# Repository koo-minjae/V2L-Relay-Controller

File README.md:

# V2L-Relay-Controller
STM32-based relay controller with manual and automatic control modes

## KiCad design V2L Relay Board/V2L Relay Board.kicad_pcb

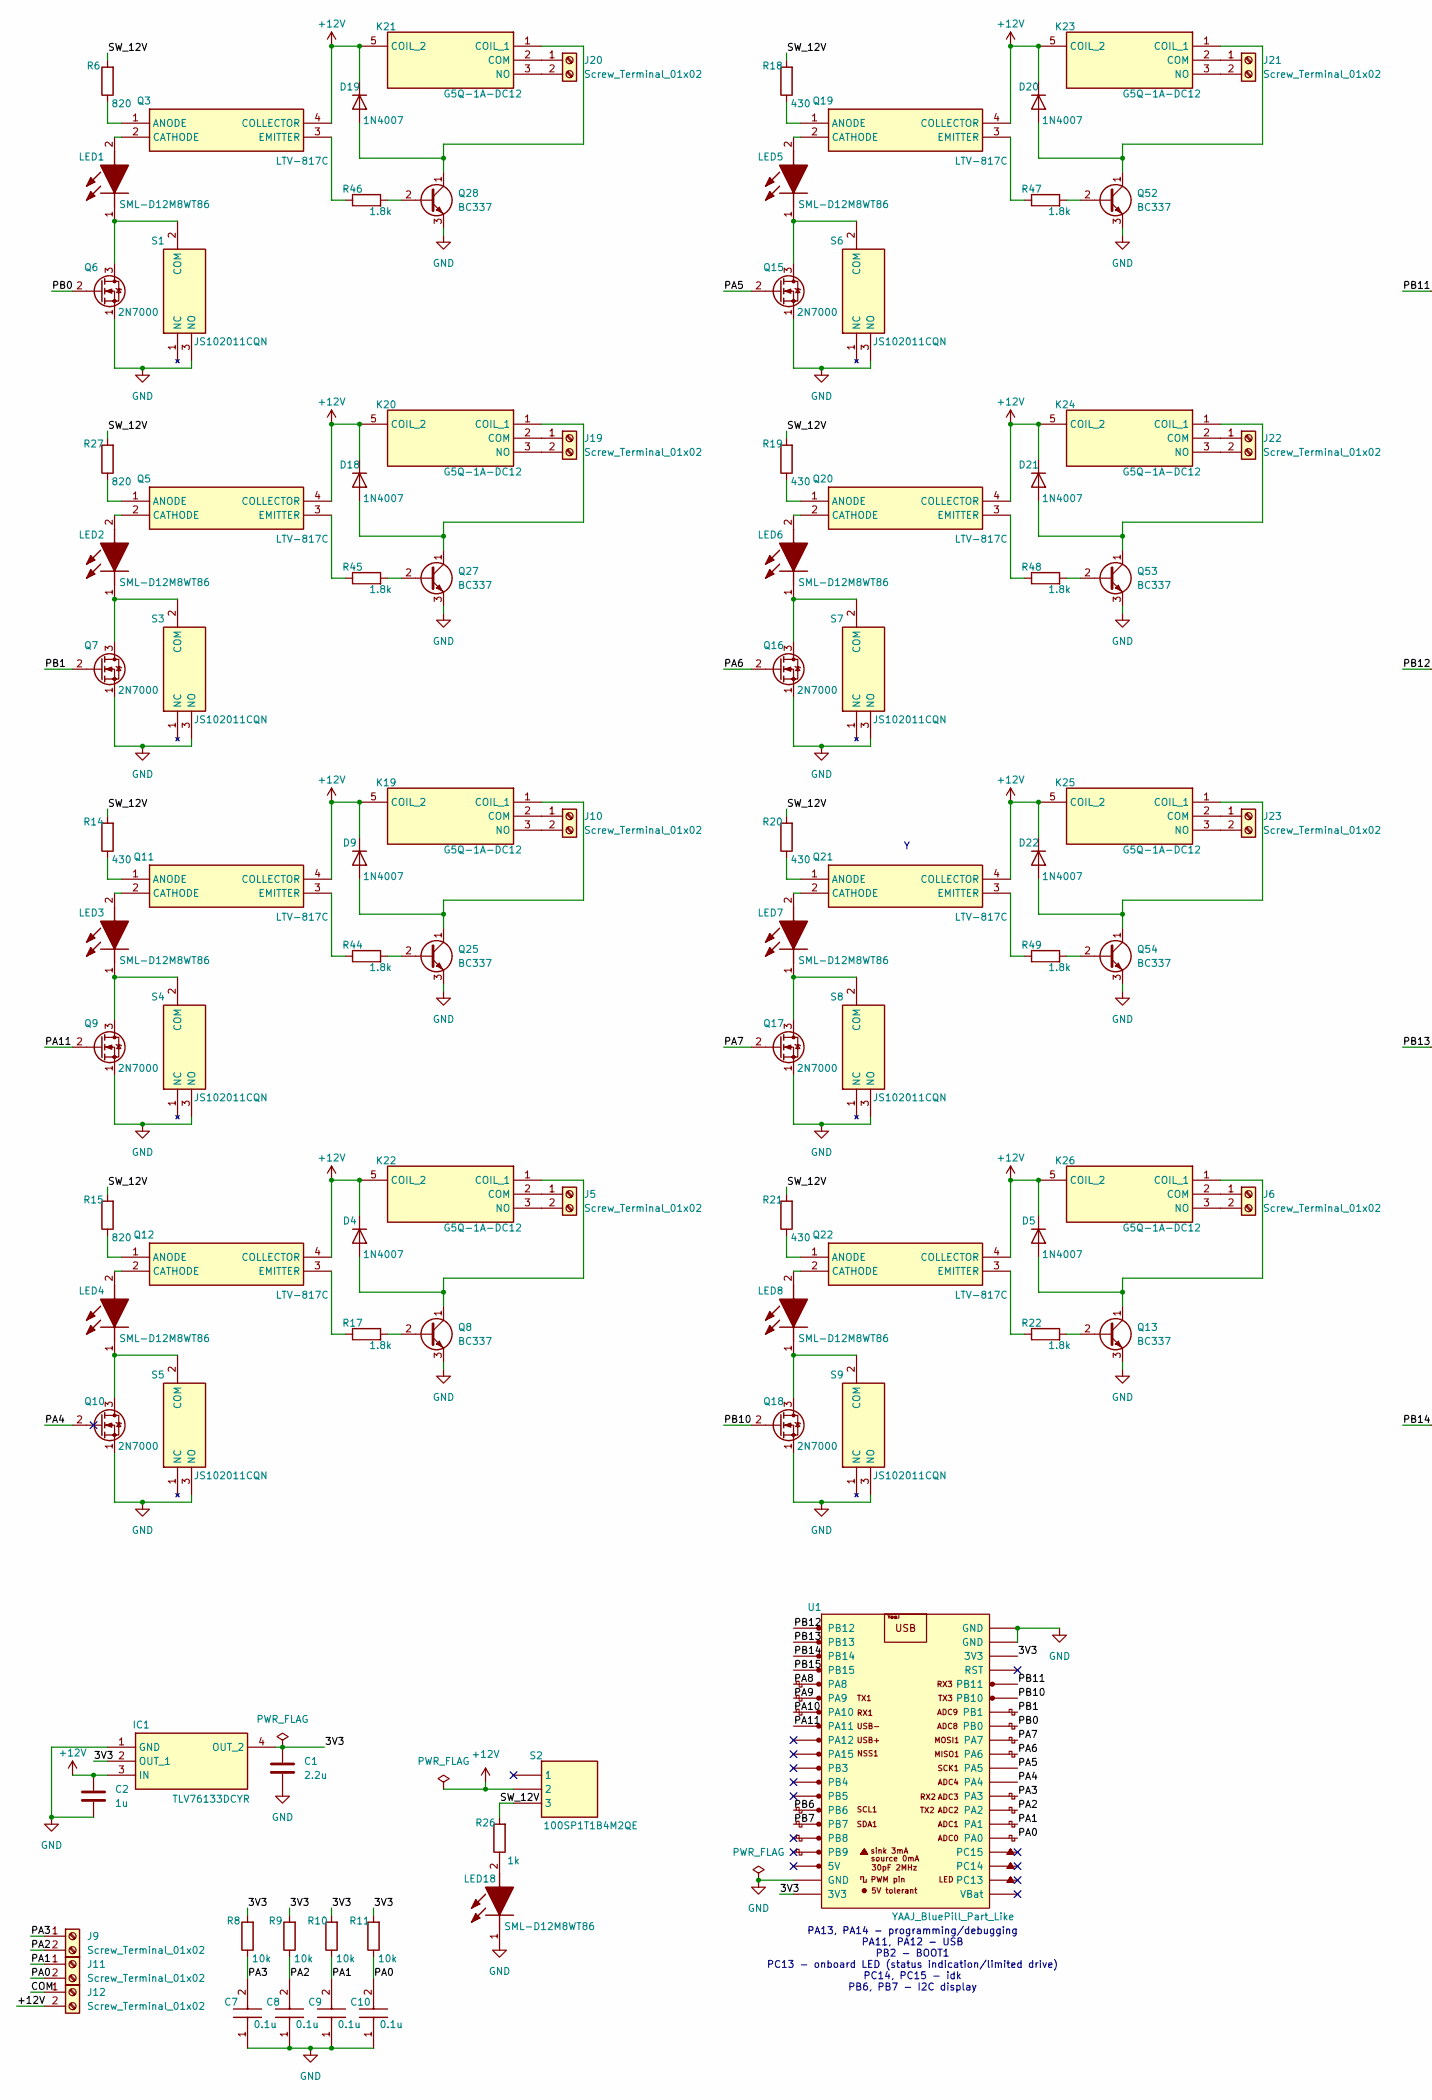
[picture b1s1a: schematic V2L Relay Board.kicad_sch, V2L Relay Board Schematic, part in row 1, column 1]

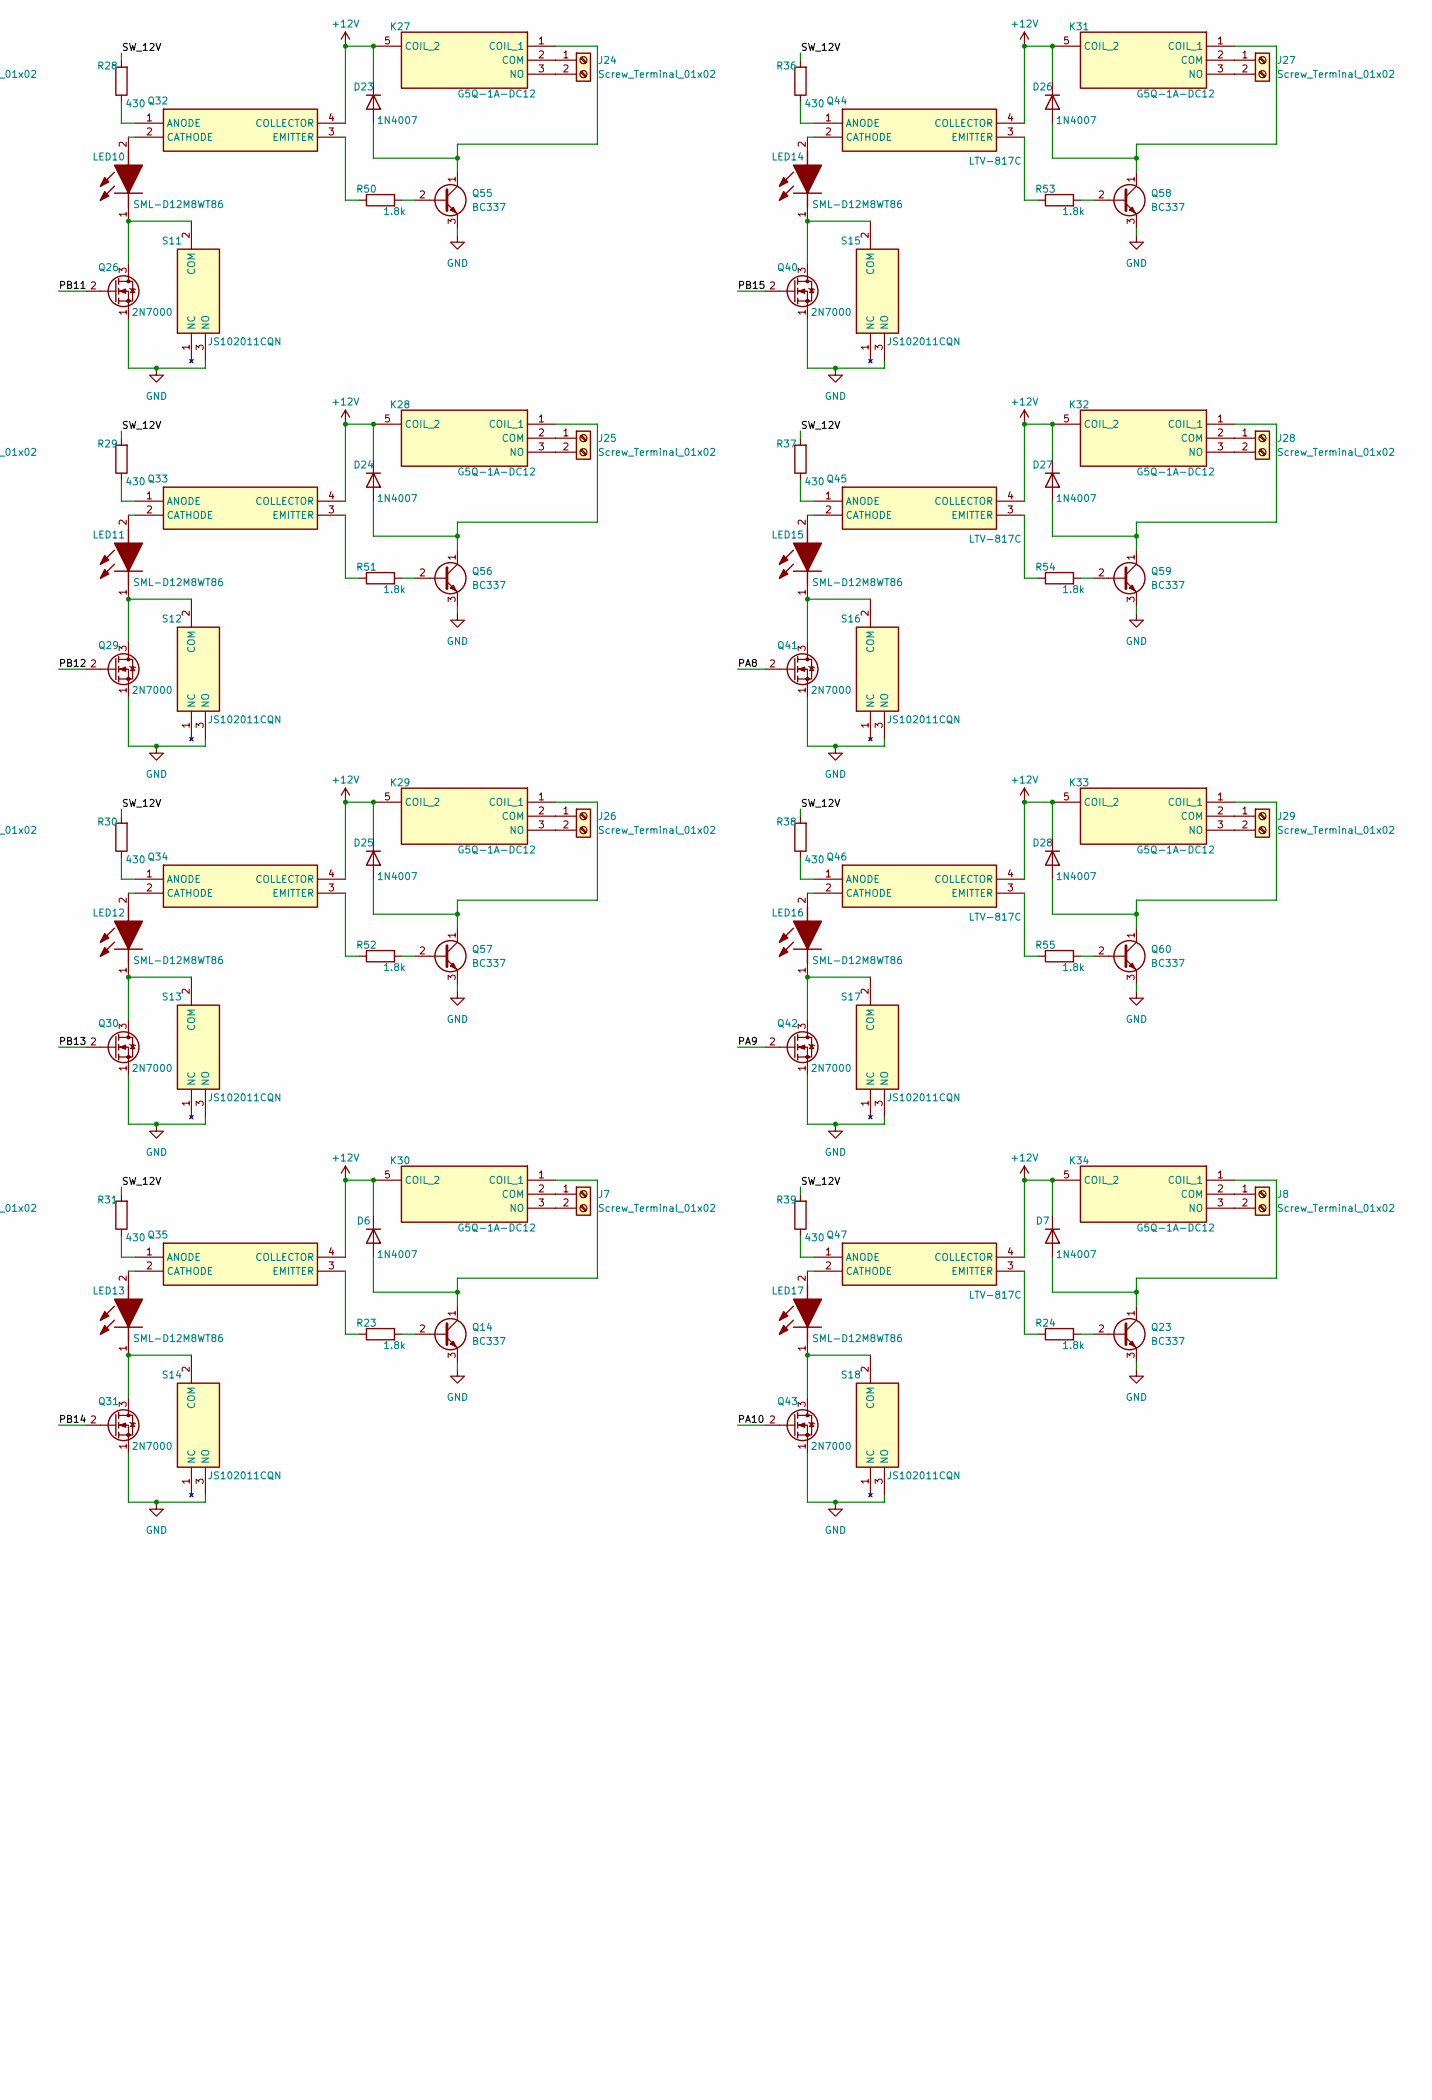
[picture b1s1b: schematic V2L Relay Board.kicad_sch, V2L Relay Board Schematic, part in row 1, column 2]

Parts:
C1: 2.2u; ZRB15x
C2: 1u; CAPC0603X35N
C7, C8, C9, C10: 0.1u; CAPC1005X60N; Manufacturer_Part_Number CL05B104KBD6PJC
D4, D5, D6, D7, D9, D18, D19, D20, D21, D22, D23, D24, D25, D26, D27, D28: 1N4007; D_DO-41_SOD81_P10.16mm_Horizontal
IC1: TLV76133DCYR; SOT230P700X180-4N; Mouser Part Number 595-TLV76133DCYR
J5, J6, J7, J8, J10, J19, J20, J21, J22, J23, J24, J25, J26, J27, J28, J29: Screw_Terminal_01x02; 1902547
J9, J11, J12: Screw_Terminal_01x02; 1729128
K19, K20, K21, K22, K23, K24, K25, K26, K27, K28, K29, K30, K31, K32, K33, K34: G5Q-1A-DC12; G5Q-1A-EL-HA-VH; Mouser Part Number 653-G5Q-1A-DC12
LED1, LED2, LED3, LED4, LED5, LED6, LED7, LED8, LED10, LED11, LED12, LED13, LED14, LED15, LED16, LED17, LED18: SML-D12M8WT86; LEDM1620X150N; Mouser Part Number 755-SML-D12M8WT86
Q3, Q5, Q11, Q12, Q19, Q20, Q21, Q22, Q32, Q33, Q34, Q35, Q44, Q45, Q46, Q47: LTV-817C; DIP762W60P254L460H450Q4N; Mouser Part Number 859-LTV-817C
Q6, Q7, Q9, Q10, Q15, Q16, Q17, Q18, Q26, Q29, Q30, Q31, Q40, Q41, Q42, Q43: 2N7000; TO-92_Inline
Q8, Q13, Q14, Q23, Q25, Q27, Q28, Q52, Q53, Q54, Q55, Q56, Q57, Q58, Q59, Q60: BC337; TO-92_Inline
R6, R15, R27: 820; ERA2AED122X
R8, R9, R10, R11: 10k; R_Axial_DIN0207_L6.3mm_D2.5mm_P10.16mm_Horizontal
R14, R18, R19, R20, R21, R28, R29, R30, R31, R36, R37, R38, R39: 430; ERA2AED122X
R17, R22, R23, R24, R44, R45, R46, R47, R48, R49, R50, R51, R52, R53, R54, R55: 1.8k; ERA6AEB101V
R26: 1k; ERA2AED122X
S1, S3, S4, S5, S6, S7, S8, S9, S11, S12, S13, S14, S15, S16, S17, S18: JS102011CQN; Mouser Part Number 611-JS102011CQN
S2: 100SP1T1B4M2QE; Mouser Part Number 612-100-A1421
U1: YAAJ_BluePill_Part_Like; YAAJ_BluePill_1

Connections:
+12V: C2.1, D4.1 (K), D5.1 (K), D6.1 (K), D7.1 (K), D9.1 (K), D18.1 (K), D19.1 (K), D20.1 (K), D21.1 (K), D22.1 (K), D23.1 (K), D24.1 (K), D25.1 (K), D26.1 (K), D27.1 (K), D28.1 (K), IC1.3 (IN), J12.2, K19.5 (COIL_2), K20.5 (COIL_2), K21.5 (COIL_2), K22.5 (COIL_2), K23.5 (COIL_2), K24.5 (COIL_2), K25.5 (COIL_2), K26.5 (COIL_2), K27.5 (COIL_2), K28.5 (COIL_2), K29.5 (COIL_2), K30.5 (COIL_2), K31.5 (COIL_2), K32.5 (COIL_2), K33.5 (COIL_2), K34.5 (COIL_2), Q3.4 (COLLECTOR), Q5.4 (COLLECTOR), Q11.4 (COLLECTOR), Q12.4 (COLLECTOR), Q19.4 (COLLECTOR), Q20.4 (COLLECTOR), Q21.4 (COLLECTOR), Q22.4 (COLLECTOR), Q32.4 (COLLECTOR), Q33.4 (COLLECTOR), Q34.4 (COLLECTOR), Q35.4 (COLLECTOR), Q44.4 (COLLECTOR), Q45.4 (COLLECTOR), Q46.4 (COLLECTOR), Q47.4 (COLLECTOR), S2.2
/3V3: C1.1, IC1.2 (OUT_1), IC1.4 (OUT_2), R8.2, R9.2, R10.2, R11.2, U1.20 (3V3), U1.38 (3V3)
/COM: J12.1
/PA0: C10.2, J11.2, R11.1, U1.25 (PA0)
/PA1: C9.2, J11.1, R10.1, U1.26 (PA1)
/PA2: C8.2, J9.2, R9.1, U1.27 (PA2)
/PA3: C7.2, J9.1, R8.1, U1.28 (PA3)
/PA4: Q10.2 (G), U1.29 (PA4)
/PA5: Q15.2 (G), U1.30 (PA5)
/PA6: Q16.2 (G), U1.31 (PA6)
/PA7: Q17.2 (G), U1.32 (PA7)
/PA8: Q41.2 (G), U1.5 (PA8)
/PA9: Q42.2 (G), U1.6 (PA9)
/PA10: Q43.2 (G), U1.7 (PA10)
/PA11: Q9.2 (G), U1.8 (PA11)
/PB0: Q6.2 (G), U1.33 (PB0)
/PB1: Q7.2 (G), U1.34 (PB1)
/PB6: U1.14 (PB6)
/PB7: U1.15 (PB7)
/PB10: Q18.2 (G), U1.35 (PB10)
/PB11: Q26.2 (G), U1.36 (PB11)
/PB12: Q29.2 (G), U1.1 (PB12)
/PB13: Q30.2 (G), U1.2 (PB13)
/PB14: Q31.2 (G), U1.3 (PB14)
/PB15: Q40.2 (G), U1.4 (PB15)
/SW_12V: R6.2, R14.2, R15.2, R18.2, R19.2, R20.2, R21.2, R26.2, R27.2, R28.2, R29.2, R30.2, R31.2, R36.2, R37.2, R38.2, R39.2, S2.3
GND: C1.2, C2.2, C7.1, C8.1, C9.1, C10.1, IC1.1 (GND), LED18.1 (K), Q6.1 (S), Q7.1 (S), Q8.3 (E), Q9.1 (S), Q10.1 (S), Q13.3 (E), Q14.3 (E), Q15.1 (S), Q16.1 (S), Q17.1 (S), Q18.1 (S), Q23.3 (E), Q25.3 (E), Q26.1 (S), Q27.3 (E), Q28.3 (E), Q29.1 (S), Q30.1 (S), Q31.1 (S), Q40.1 (S), Q41.1 (S), Q42.1 (S), Q43.1 (S), Q52.3 (E), Q53.3 (E), Q54.3 (E), Q55.3 (E), Q56.3 (E), Q57.3 (E), Q58.3 (E), Q59.3 (E), Q60.3 (E), S1.3 (NO), S3.3 (NO), S4.3 (NO), S5.3 (NO), S6.3 (NO), S7.3 (NO), S8.3 (NO), S9.3 (NO), S11.3 (NO), S12.3 (NO), S13.3 (NO), S14.3 (NO), S15.3 (NO), S16.3 (NO), S17.3 (NO), S18.3 (NO), U1.19 (GND), U1.39 (GND), U1.40 (GND)
unnamed: D4.2 (A), K22.1 (COIL_1), Q8.1 (C)
unnamed: D5.2 (A), K26.1 (COIL_1), Q13.1 (C)
unnamed: D6.2 (A), K30.1 (COIL_1), Q14.1 (C)
unnamed: D7.2 (A), K34.1 (COIL_1), Q23.1 (C)
unnamed: D9.2 (A), K19.1 (COIL_1), Q25.1 (C)
unnamed: D18.2 (A), K20.1 (COIL_1), Q27.1 (C)
unnamed: D19.2 (A), K21.1 (COIL_1), Q28.1 (C)
unnamed: D20.2 (A), K23.1 (COIL_1), Q52.1 (C)
unnamed: D21.2 (A), K24.1 (COIL_1), Q53.1 (C)
unnamed: D22.2 (A), K25.1 (COIL_1), Q54.1 (C)
unnamed: D23.2 (A), K27.1 (COIL_1), Q55.1 (C)
unnamed: D24.2 (A), K28.1 (COIL_1), Q56.1 (C)
unnamed: D25.2 (A), K29.1 (COIL_1), Q57.1 (C)
unnamed: D26.2 (A), K31.1 (COIL_1), Q58.1 (C)
unnamed: D27.2 (A), K32.1 (COIL_1), Q59.1 (C)
unnamed: D28.2 (A), K33.1 (COIL_1), Q60.1 (C)
unnamed: J5.1, K22.2 (COM)
unnamed: J5.2, K22.3 (NO)
unnamed: J6.1, K26.2 (COM)
unnamed: J6.2, K26.3 (NO)
unnamed: J7.1, K30.2 (COM)
unnamed: J7.2, K30.3 (NO)
unnamed: J8.1, K34.2 (COM)
unnamed: J8.2, K34.3 (NO)
unnamed: J10.1, K19.2 (COM)
unnamed: J10.2, K19.3 (NO)
unnamed: J19.1, K20.2 (COM)
unnamed: J19.2, K20.3 (NO)
unnamed: J20.1, K21.2 (COM)
unnamed: J20.2, K21.3 (NO)
unnamed: J21.1, K23.2 (COM)
unnamed: J21.2, K23.3 (NO)
unnamed: J22.1, K24.2 (COM)
unnamed: J22.2, K24.3 (NO)
unnamed: J23.1, K25.2 (COM)
unnamed: J23.2, K25.3 (NO)
unnamed: J24.1, K27.2 (COM)
unnamed: J24.2, K27.3 (NO)
unnamed: J25.1, K28.2 (COM)
unnamed: J25.2, K28.3 (NO)
unnamed: J26.1, K29.2 (COM)
unnamed: J26.2, K29.3 (NO)
unnamed: J27.1, K31.2 (COM)
unnamed: J27.2, K31.3 (NO)
unnamed: J28.1, K32.2 (COM)
unnamed: J28.2, K32.3 (NO)
unnamed: J29.1, K33.2 (COM)
unnamed: J29.2, K33.3 (NO)
unnamed: LED1.2 (A), Q3.2 (CATHODE)
unnamed: LED1.1 (K), Q6.3 (D), S1.2 (COM)
unnamed: LED2.2 (A), Q5.2 (CATHODE)
unnamed: LED2.1 (K), Q7.3 (D), S3.2 (COM)
unnamed: LED3.2 (A), Q11.2 (CATHODE)
unnamed: LED3.1 (K), Q9.3 (D), S4.2 (COM)
unnamed: LED4.2 (A), Q12.2 (CATHODE)
unnamed: LED4.1 (K), Q10.3 (D), S5.2 (COM)
unnamed: LED5.2 (A), Q19.2 (CATHODE)
unnamed: LED5.1 (K), Q15.3 (D), S6.2 (COM)
unnamed: LED6.2 (A), Q20.2 (CATHODE)
unnamed: LED6.1 (K), Q16.3 (D), S7.2 (COM)
unnamed: LED7.2 (A), Q21.2 (CATHODE)
unnamed: LED7.1 (K), Q17.3 (D), S8.2 (COM)
unnamed: LED8.2 (A), Q22.2 (CATHODE)
unnamed: LED8.1 (K), Q18.3 (D), S9.2 (COM)
unnamed: LED10.2 (A), Q32.2 (CATHODE)
unnamed: LED10.1 (K), Q26.3 (D), S11.2 (COM)
unnamed: LED11.2 (A), Q33.2 (CATHODE)
unnamed: LED11.1 (K), Q29.3 (D), S12.2 (COM)
unnamed: LED12.2 (A), Q34.2 (CATHODE)
unnamed: LED12.1 (K), Q30.3 (D), S13.2 (COM)
unnamed: LED13.2 (A), Q35.2 (CATHODE)
unnamed: LED13.1 (K), Q31.3 (D), S14.2 (COM)
unnamed: LED14.2 (A), Q44.2 (CATHODE)
unnamed: LED14.1 (K), Q40.3 (D), S15.2 (COM)
unnamed: LED15.2 (A), Q45.2 (CATHODE)
unnamed: LED15.1 (K), Q41.3 (D), S16.2 (COM)
unnamed: LED16.2 (A), Q46.2 (CATHODE)
unnamed: LED16.1 (K), Q42.3 (D), S17.2 (COM)
unnamed: LED17.2 (A), Q47.2 (CATHODE)
unnamed: LED17.1 (K), Q43.3 (D), S18.2 (COM)
unnamed: LED18.2 (A), R26.1
unnamed: Q3.1 (ANODE), R6.1
unnamed: Q3.3 (EMITTER), R46.1
unnamed: Q5.1 (ANODE), R27.1
unnamed: Q5.3 (EMITTER), R45.1
unnamed: Q8.2 (B), R17.2
unnamed: Q11.1 (ANODE), R14.1
unnamed: Q11.3 (EMITTER), R44.1
unnamed: Q12.1 (ANODE), R15.1
unnamed: Q12.3 (EMITTER), R17.1
unnamed: Q13.2 (B), R22.2
unnamed: Q14.2 (B), R23.2
unnamed: Q19.1 (ANODE), R18.1
unnamed: Q19.3 (EMITTER), R47.1
unnamed: Q20.1 (ANODE), R19.1
unnamed: Q20.3 (EMITTER), R48.1
unnamed: Q21.1 (ANODE), R20.1
unnamed: Q21.3 (EMITTER), R49.1
unnamed: Q22.1 (ANODE), R21.1
unnamed: Q22.3 (EMITTER), R22.1
unnamed: Q23.2 (B), R24.2
unnamed: Q25.2 (B), R44.2
unnamed: Q27.2 (B), R45.2
unnamed: Q28.2 (B), R46.2
unnamed: Q32.1 (ANODE), R28.1
unnamed: Q32.3 (EMITTER), R50.1
unnamed: Q33.1 (ANODE), R29.1
unnamed: Q33.3 (EMITTER), R51.1
unnamed: Q34.1 (ANODE), R30.1
unnamed: Q34.3 (EMITTER), R52.1
unnamed: Q35.1 (ANODE), R31.1
unnamed: Q35.3 (EMITTER), R23.1
unnamed: Q44.1 (ANODE), R36.1
unnamed: Q44.3 (EMITTER), R53.1
unnamed: Q45.1 (ANODE), R37.1
unnamed: Q45.3 (EMITTER), R54.1
unnamed: Q46.1 (ANODE), R38.1
unnamed: Q46.3 (EMITTER), R55.1
unnamed: Q47.1 (ANODE), R39.1
unnamed: Q47.3 (EMITTER), R24.1
unnamed: Q52.2 (B), R47.2
unnamed: Q53.2 (B), R48.2
unnamed: Q54.2 (B), R49.2
unnamed: Q55.2 (B), R50.2
unnamed: Q56.2 (B), R51.2
unnamed: Q57.2 (B), R52.2
unnamed: Q58.2 (B), R53.2
unnamed: Q59.2 (B), R54.2
unnamed: Q60.2 (B), R55.2

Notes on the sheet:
PA13, PA14 - programming/debugging PA11, PA12 - USB PB2 - BOOT1 PC13 - onboard LED (status indication/limited drive) PC14, PC15 - idk PB6, PB7 - I2C display

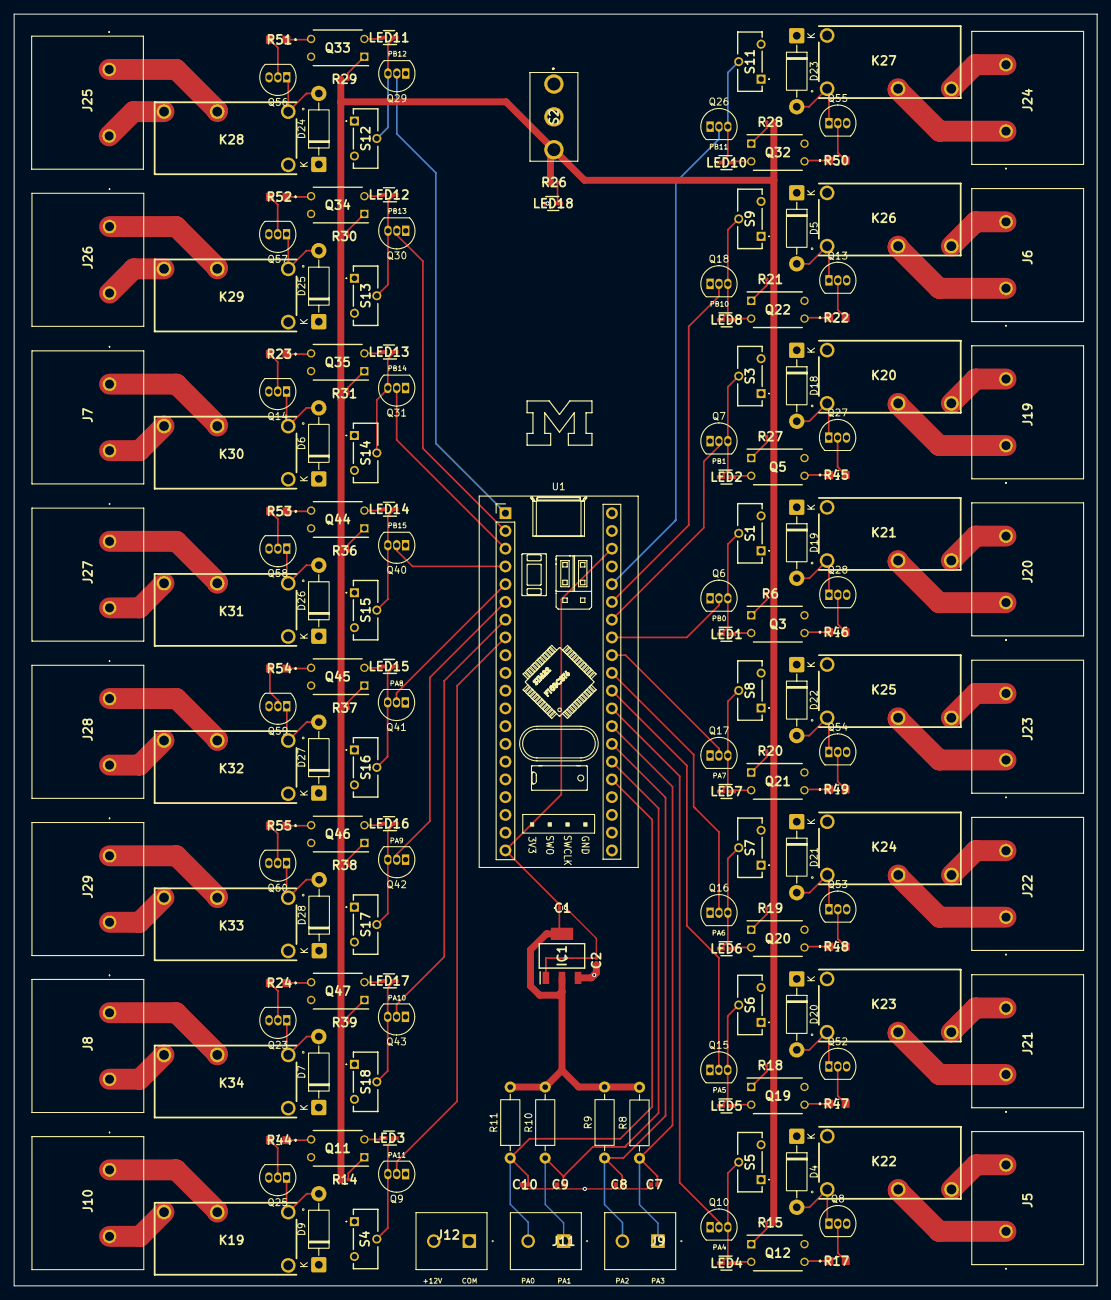
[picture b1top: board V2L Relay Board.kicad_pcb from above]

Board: 4 copper layers, 155.0 x 182.0 mm, 178 parts (0 on the bottom side), 153 nets.
